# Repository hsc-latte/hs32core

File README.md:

# Processor

Open Source Hardware Processor

# Mission
- Reduce the barrier to entry to open source silicon for hobbyists
- Encourage the production usage of fully open source, royalty-free, community designed ASICs within the maker community (displace proprietary chip designs)
- Shorten the iteration time from ideation to fabrication
- Explore creative ideas not found in current hardware offerings
- Interoperate with modern, high performance components that are typically the realm of proprietary designs (DDR4, PCIE root complex, USB3, etc come to mind)
- Make easy to use, relatively inexpensive hardware that people can acutally buy

# Project Goals

## Processor V1 (November 2020)
The software and the hardware parts can mostly be done simultaneously.
1. Create a new CPU instruction set and design.
    - it should be a sort of minimum viable 32 bit CPU. Something similar in capability to an Arduino, and with similar ports.
2. Test the CPU design in simulators and on FPGA
3. Fabricate the processor using Google and efabless free shuttle service for open source using 130nm process, and open source PDK
    - Submit a design for the November free shuttle run.
    - Try not to go too crazy with transistor count. We want to not be dependent on free fabrication in the future.
4. Build an assembler for the ISA
5. Make an Arduino-like board for the processor, with similar capabilities and supporting software
6. Write or port C toolchain. Some higher level languages would also be nice, such as JS/python.
    - [TCC](https://bellard.org/tcc/) may be a good compiler to retarget for C.
        - [Here](https://bellard.org/tcc/tcc-doc.html#CPU-dependent-code-generation) is what would be needed to be done to retarget it.
    - Port as much of libc as possible. [Uclib-ng](https://www.uclibc-ng.org/) or [newlib](https://sourceware.org/newlib/) would be good options.

### Task List for V1 by Early November 2020 (exact deadline date to be determined):
- Design FPGA carrier board PCB. Get it manufactured, into peoples hands.
  - This board has this FPGA board on it, https://www.robotshop.com/en/devantech-icewerx-ice40-hx8k-fpga.html?utm_source=google&utm_medium=surfaces&utm_campaign=surfaces_across_google_usen&gclid=EAIaIQobChMI5cem_Lyv6wIV0yCtBh2KFQhIEAYYASABEgJyuvD_BwE
  - The board has SRAM and Flash chips built in.
  - The board has latch chips to function as IO expanders because the fabricated CPU will be pin-limited.
  - The board should have its own clock IC.
- Design ISA
- Write assembler for the ISA
- Get Verilog simulator up and running and documented.
- Design CPU and peripherals in Verilog or Migen. 
- Simulate CPU and periherals in software. Programs should be able to run and take input/output. 
- Test CPU and peripherals on the FGPA carrier board. RAM and flash should work. We should be able to load an run real programs on the board
- Create task list to prepare the verilog design for fabrication.
  - Ensure we haven't overlooked anything that could cause our design to be rejected by Google/Skywater
  - Ensure our design might actually work when fabricated

**Fun Side Project for V1** : Make an Apple II or commodore style standalone PC using the processsor.

## Processor V2 (Early 2021)
1. Replicate V1 using non-donated fabrication and make the process economically sustainable.
    - This means making chips and boards than people can actually buy.
    - See Target Silicon section below.
    - In theory, multi project wafer runs on very old tech could be < $100 per chip. Costs will go down as volume increases.
    - we could do a Kickstarter or similar to fund a larger fabrication run for V2.
2. Expand capabilities with software support
    - more RAM, faster RAM
    - graphics framebuffer
    - more ports in general.
3. Port other languages.
    - [MicroPython](https://micropython.org/) may be a good option.
    - Build a [LLVM backend](https://www.llvm.org/docs/WritingAnLLVMBackend.html).
        - This is a lot of work, so it could be done in V2 or V3.
4. A basic OS. This would be similar to old computers running BASIC. This may be porting an existing OS or writing one from sratch. 

## Processor V3 (Late 2021)
While maintaining economic sustainability:
1. Expand capabilities with software support
    - add MMU (ucLinux will run without an MMU, but typical programs will not run. They require fork() and mmap() among other MMU features.)
    - hardware floating point
    - more RAM, faster RAM
    - more ports in general. HDMI, ethernet, possibly USB and WiFi to some degree, with external chips
2. Make a raspberry-Pi style board. It would be much much slower than a Pi, but should have a similar style of capabilities and functions.
3. Port more software to the system
    - glibc should be able to be ported at this stage
4. Explore Linux support

## Processor V4 (2022)
Generally more powerful and unique. Try to achieve some interoperability with modern hardware, yet remain fully open source.
Just some ideas:
- On-chip Software Defined Radio (SDR) so that it can be a flexible radio device (WiFi, LTE, Bluetooth, GPS)
- GPU
- Multi core
- PCIE Root Controller
- DDR4 Controller
- USB3 Controller

# Educational Resources
- Reading list for newcomers to computer engineering, started here: [link](Resources.md)

# CPU for V1

- 32 bit
- flat address space, no MMU
- As simple as possible
- Should support running unmodified C programs.
- Required math ops: the usual AND OR NOT XOR shifts, rotates.
- Integer multiply and divide would be cool if we can fit it.
- Floating point math would be cool if we can fit it, including addition,mul,div operations

# Ports for V1
The general idea is to have a superset of the peripherals that the old Arduino has.
- 14 digital 1/0
- 6 pins with PWM
- 6 analog input
  - 8 channel SPI ADC https://www.digikey.com/product-detail/en/microchip-technology/MCP3008T-I-SL/MCP3008T-I-SLCT-ND/5148847
- 4 channel SPI DAC https://www.digikey.com/product-detail/en/texas-instruments/TLV5620IDR/296-41707-2-ND/1669684
- SPI/I2C/I2S	1/1/1
- SRAM: http://www.issi.com/WW/pdf/62WV12816ALL.pdf
- Flash: S29AL008J https://www.cypress.com/file/216396/download
- External Clock of at least 16mhz
- USB port for programming (FTDI chip?)
- PS2 mouse, keyboard
  - https://opencores.org/projects/ps2
- 4 Serial Ports (UART)
  - https://opencores.org/projects/uart16550
  - https://opencores.org/projects/uart
- Ethernet
  - Ethernet likely takes too many gates, but we can have an external chip:
  - Using this chip which offloads most of the harder networking work and you just need to talk to it over SPI.
   - https://wizwiki.net/wiki/lib/exe/fetch.php?media=products:w5100s:w5100s_ds_v100e.pdf
   - https://www.digikey.com/products/en?keywords=W5100S
   - in fact it does TCP and UDP for you!
- Display: NTSC Composite Video Out
  - ntsc https://webcache.googleusercontent.com/search?q=cache:4BF235L2FPcJ:https://opencores.org/projects/fbas_encoder+&cd=1&hl=en&ct=clnk&gl=us
- SD Card or Compactflash or something similar
- If we want we can add a USB host using an external chip https://www.hobbytronics.co.uk/usb-host-dip

# Target Silicon:
### Google-skywater november 2020 free shuttle run
- Info collected from skywater-pdk slack:
- Tim Edwards: The whole chip will be (provisionally) 3.2 x 5.3, but the user area will be about 9 to 10 mm^2.  That is not including the pad frame;  that's the full core area you get to use.  I'm aiming to keep the "management region" off to one side to keep the user area roughly square.  The pads are 200um high, so the height is limited to 2.8mm, so the area you get to work with will be around 3.2 to 3.5mm wide and 2.8mm high.
- Packaging: WLCSP: Main reason for wlcsp packaging is reduced parasitics for high speed signals like SERDES etc. Wlcsp is done before cutting the wafer so it doesn't require a separate packaging line.
- Pins: Expected usable pins is more ~ 40

### Non-Google, more sustainable options:
- Silicon price list exploration: https://docs.google.com/spreadsheets/d/1oqIo1lJNRx8SugjHd8WOBk07iPeCCzOLdnaOR9BBdXU/edit#gid=0
- 700nm process from ON Semi 
- 5 mm^2 of this tech: ON Semi 0.7µ C07M-D 2M/1P
- Silicon Fab price list: https://europractice-ic.com/wp-content/uploads/2020/07/General-MPW-EUROPRACTICE-200714-v11.pdf
- Another price list from europractice... https://europractice-ic.com/wp-content/uploads/2020/05/Miniasic-MPW-EUROPRACTICE-200505-v5.pdf
- Packaging: https://europractice-ic.com/packaging-integration/standard-packaging/
- Bond pad design for wirebonding https://europractice-ic.com/wp-content/uploads/2020/06/ASIC-Package-Design-Rules-10062020.pdf
- How many pins can the processor have? chip side length/distance between pads: sqrt(5mm^2) / 65um = 34. To be conservative, round to 30 pads per side. Therefore, estimate maximum 120 total pins for the entire chip. Ceramic quad flat pack (QFP) is available with that many pins from europractice.
- How much of the die area is dedicated to wire bonding pads? Assume bond pad is 60um. 4 * 60um * sqrt(5mm^2) = .536 mm^2
  - Therefore approximately 10% of the die ares is wire bonding pads. Not too bad.
- I would guess theres about 30000 to 8000 transistors per mm^2
- Therefore at 5mm^2, we have 150k to 40k transistors per chip. (it will be less due to the edge ring area being used for other stuff)
- It should be 4 transistors per gate
- so 37k to 10k gates per chip
- on-chip memory:
  - It looks like a CMOS SRAM cell has 6 transistors ... for 1 bit of storage.
  - If the entire die was made into SRAM we would therefore get 25kbit to 6.6kbit, or 3.2KB to .8KB
- The most basic ZPU (which is a tiny processor) calls for "about 1700 gates"

# Interesting Tools

- Long list of companies offering Multi Project Wafer services https://www.mirrorsemi.com/Foundry.html
- A Python toolbox for building complex digital hardware https://github.com/m-labs/migen
- Generates a custom CPU based on C code tailored to your code https://github.com/dawsonjon/Chips-2.0
- Open Source VLSI toolbox http://opencircuitdesign.com/magic/
- EDAlyze - python scripting of EDA tools https://github.com/olofk/edalize
- Package manager for IP cores https://github.com/olofk/fusesoc
- *** OpenLane - fully automated RTL to ASIC flow. https://github.com/efabless/openlane
- APIO - open ecosystem for FPGA boards https://github.com/FPGAwars/apio
- 130nm process design kit (PDK) from skywater https://github.com/google/skywater-pdk

# License 

- GPL v3

# VGA Notes
  - https://webcache.googleusercontent.com/search?q=cache:uBfl2FENLigJ:https://opencores.org/projects/yavga+&cd=2&hl=en&ct=clnk&gl=us
  - really not sure if we can do video out without a framebuffer, and then if we can get fast enough external RAM to use as a framebuffer.
  - possible expensive memory chip: https://www.digikey.com/product-detail/en/renesas-electronics-america-inc/70V28L20PFGI/800-2108-ND/2010195
   - it is dual port so it can simultaneous read and write (great for framebuffers)
   - asynchronous SRAM
   - parallel addr/data bus, 16 bit
   - full speed should be 50Mhz @ 16 bit accesses
   - The VGA core has a 50Mhz pixel clock so it should be possible to do color at 800x600!

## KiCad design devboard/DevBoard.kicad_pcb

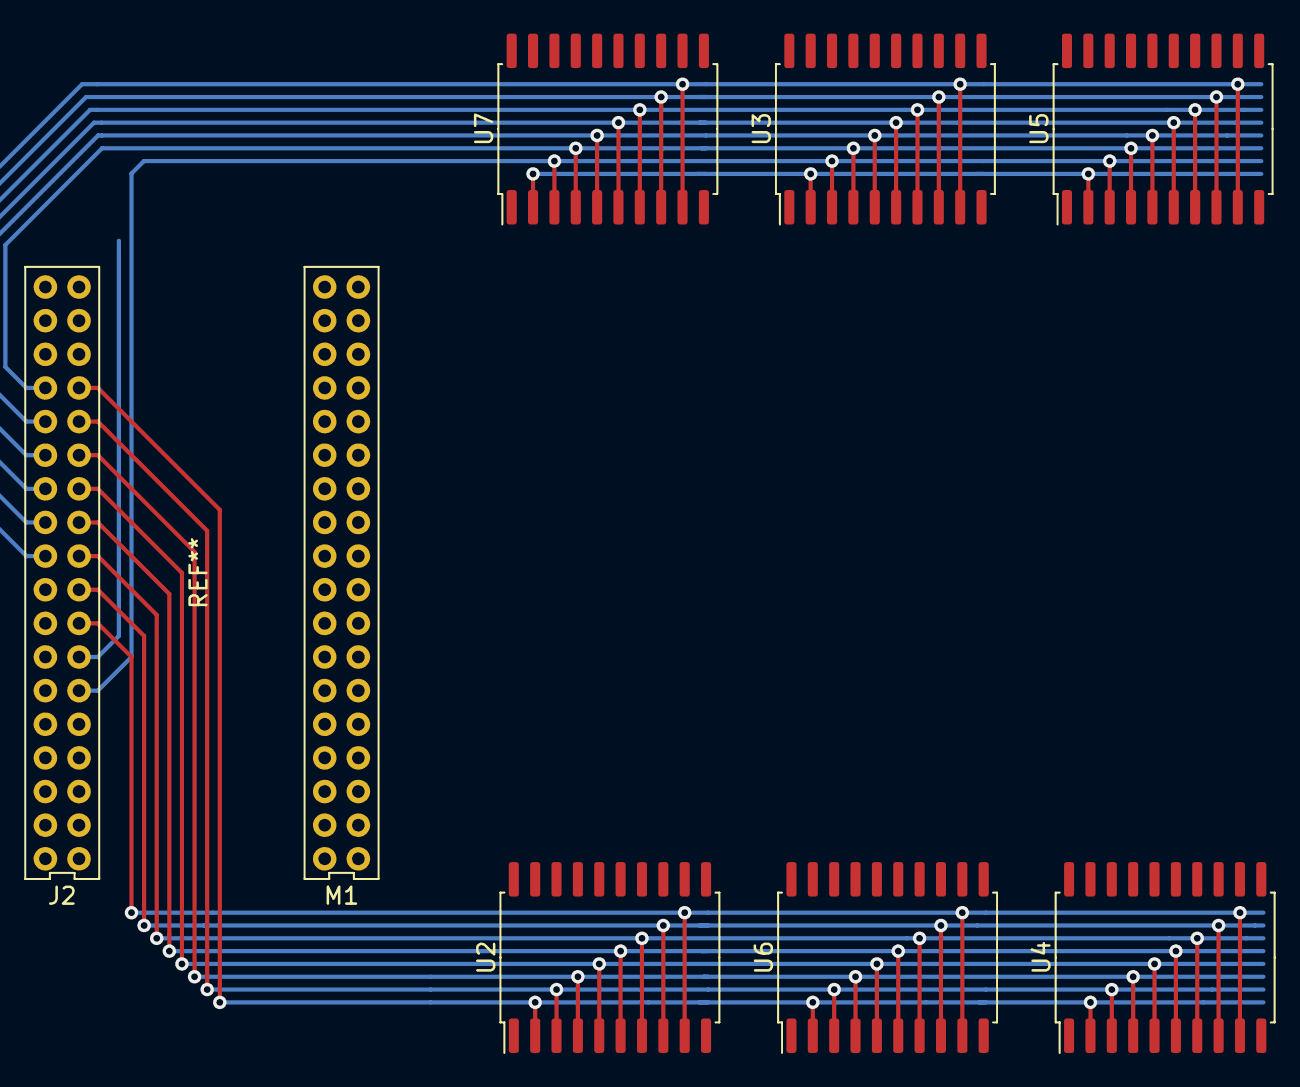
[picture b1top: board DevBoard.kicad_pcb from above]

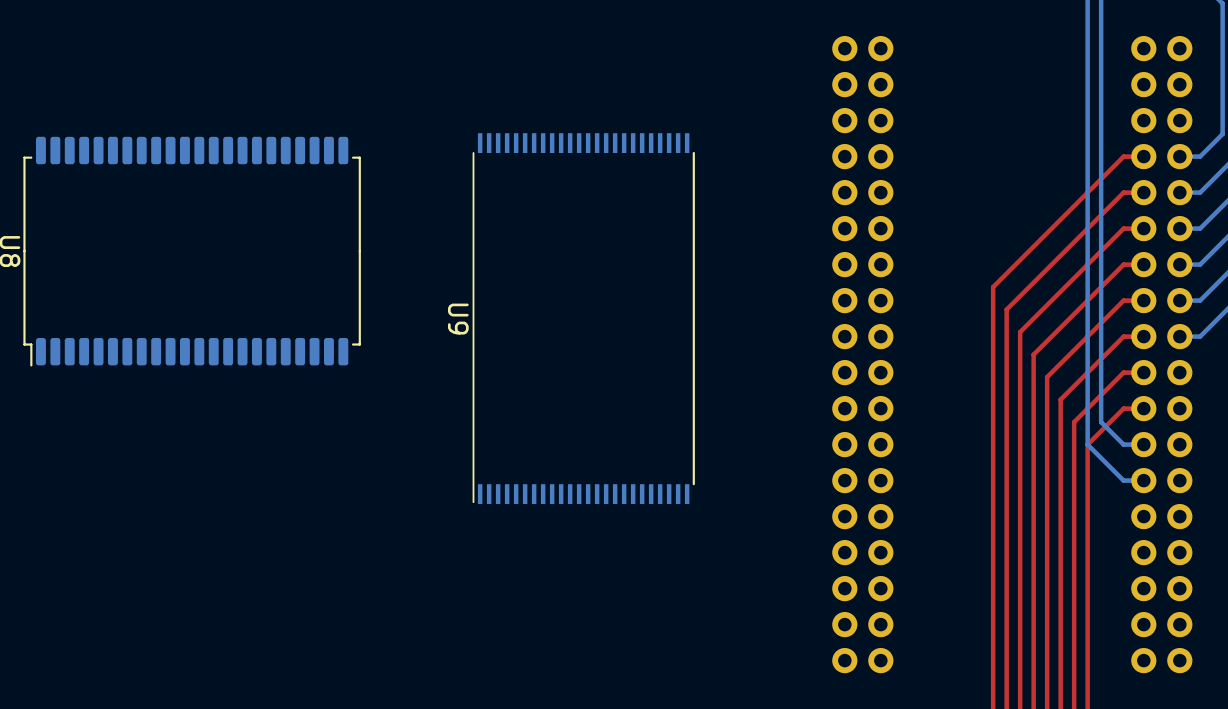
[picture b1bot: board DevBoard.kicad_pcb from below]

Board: 2 copper layers, 9 parts (2 on the bottom side), 43 nets.

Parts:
M1: icewerx; iceWerx
U2, U3, U4, U5: 74HC573; SOIC-20W_7.5x12.8mm_P1.27mm
U6, U7: 74HC245; SOIC-20W_7.5x12.8mm_P1.27mm
U8: IS62WV12816ALL; TSOP-II-44_10.16x18.41mm_P0.8mm
U9: S29AL008J70TFI013; TSOP-I-48_18.4x12mm_P0.5mm

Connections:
+3V3: U2.20, U3.20, U4.20, U5.20, U6.20, U7.20
/3.3V: U8.11, U8.33, U9.12, U9.14, U9.37, U9.47
/A0: U2.19, U8.5, U8.39, U9.25
/A1: U2.18, U8.4, U9.24
/A2: U2.17, U8.3, U9.23
/A3: U2.16, U8.2, U9.22
/A4: U2.15, U8.1, U9.21
/A5: U2.14, U8.44, U9.20
/A6: U2.13, U8.43, U9.19
/A7: U2.12, U8.42, U9.18
/A8: U3.19, U8.27, U9.8
/A9: U3.18, U8.26, U9.7
/A10: U3.17, U8.25, U9.6
/A11: U3.16, U8.24, U9.5
/A12: U3.15, U8.22, U9.4
/A13: U3.14, U8.21, U9.3
/A14: U3.13, U8.20, U9.2
/A15: U3.12, U8.19, U9.1
/A16: U4.19, U8.18, U9.48
/A17: U4.18, U9.17
/A18: U4.17, U9.16
/A30: U5.13, U9.26
/A31: U5.12, U8.6
/ALE1: U4.11, U5.11
/IO0: M1.J2.30, U2.2, U4.2, U6.2, U8.7, U9.29
/IO1: M1.J2.28, U2.3, U4.3, U6.3, U8.8, U9.31
/IO2: M1.J2.26, U2.4, U4.4, U6.4, U8.9, U9.33
/IO3: M1.J2.24, U2.5, U4.5, U6.5, U8.10, U9.35
/IO4: M1.J2.22, U2.6, U4.6, U6.6, U8.13, U9.38
/IO5: M1.J2.20, U2.7, U4.7, U6.7, U8.14, U9.40
/IO6: M1.J2.18, U2.8, U4.8, U6.8, U8.15, U9.42
/IO7: M1.J2.16, U2.9, U4.9, U6.9, U8.16, U9.44
/IO8: M1.J2.14, U3.2, U5.2, U7.2, U8.29, U9.30
/IO9: M1.J2.12, U3.3, U5.3, U7.3, U8.30, U9.32
/IO10: M1.J2.29, U3.4, U5.4, U7.4, U8.31, U9.34
/IO11: M1.J2.27, U3.5, U5.5, U7.5, U8.32, U9.36
/IO12: M1.J2.25, U3.6, U5.6, U7.6, U8.35, U9.39
/IO13: M1.J2.23, U3.7, U5.7, U7.7, U8.36, U9.41
/IO14: M1.J2.21, U3.8, U5.8, U7.8, U8.37, U9.43
/IO15: M1.J2.19, U3.9, U5.9, U7.9, U8.38, U9.45
/OE: U6.19, U7.19
/WE: U6.1, U7.1, U8.17, U9.11
GND: U2.10, U3.1, U3.10, U4.1, U4.10, U5.1, U5.10, U6.10, U7.10, U8.12, U8.34, U8.41, U9.27, U9.28, U9.46

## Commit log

2020-07-30 add some links to open cores and some hardware
2020-07-31 add a simple python emulator
2020-08-02 Update LICENSE
2020-08-04 rename
2020-08-07 Create Resources.md
    wiki type file for general knowledge resources
2020-08-10 Add mission
2020-08-11 Added magic tool
2020-08-11 Added yosys and misc changes
    Added yosys, added source github repo to README.md, and echoed the link
    of the VNC client for the magic tool when run.
2020-08-11 Reformatted tools/README.md and added docker sources
2020-08-17 Add some google-skywater info
2020-08-18 Added software goals to project goals
2020-08-22 Addded documentation and timing
2020-08-22 Edits
2020-08-26 wiznet chip link
2020-08-29 Rough draft of ISA
    Rough draft of a 32-bit hex ISA
2020-08-29 Updated some things
2020-08-29 Updated documentation.
2020-08-29 Yes oops forgot about this one.
2020-08-31 add docker notes for RTL stuff
2020-08-31 Updated rtl/README
2020-08-31 get APIO packages installed properly
2020-08-31 Updated CPU.md
2020-08-31 Added Development PCB Schematic
2020-09-01 Added Flash
2020-09-05 Updates v2
2020-09-07 Partially completed instruction set
2020-09-08 Update ISA
2020-09-09 Minor adjustment to ISA
2020-09-11 Add ADDI instruction
2020-09-12 update verilator in docker - get a test verilator running
2020-09-12 add some hacked together wbuart
2020-09-12 add docker stuff for wbuart
2020-09-13 Board modifications
2020-09-14 Updated ISA
2020-09-14 Table
2020-09-14 Try again haha
2020-09-14 Pretty?
2020-09-14 Revert!
2020-09-19 Oh well
2020-09-19 add opcodes for new emulator
2020-09-21 Idk...
2020-09-23 No more Rm Rn operands!
2020-09-23 Update ISA encoding and table
2020-09-24 Update ISA J-Type encoding
2020-09-24 Scanner, CLI, and Dockerfile for the assembler
2020-09-24 Added small README.md
2020-09-24 Remove lock file
2020-09-26 K there
2020-09-26 Updated block
2020-09-26 remove uart example
2020-09-26 new devboard project so i can do this in altium faster
2020-09-27 footprint and symbols
2020-09-27 working on FPs and symbs
2020-09-27 working on schematic
2020-09-27 made some schematic changes. added gitignore. added somemore files.added pdf for viewing
2020-09-27 schematic work. new pdf.
2020-09-27 schematic work. updated pdf. shifted A0 out for BLE
2020-09-28 schematic work. updated pdf.
2020-09-28 annotated. imported to pdf. assigned some FPs
2020-09-29 Adds parser for the assembler
    This parses the op codes. checks the instructions have the right arity,
    and checks that the values have valid types (e.g register or imm)
    This also builds a symbol table for the labels.
    This also does some refactoring here and there.
2020-09-29 schematic work. finalizing address pins, etc. adding more peripherals. latest pdf generated.
2020-09-29 updated git ignore
2020-09-29 schematic work, placed LDO
2020-09-30 finished up schematic for now
2020-09-30 updated power input to allow for 5v external power. added debounce cap to reset button. printed new pdf
2020-09-30 working on pcb
2020-09-30 layout work
2020-10-02 layout work. completed intial data bus routing
2020-10-02 layout work. control signals
2020-10-02 layout work. GPIO. reset
2020-10-03 layout work. mainly routed
2020-10-03 layout work. clearing drc. printed prints
2020-10-03 designators. cleanup.new prints
2020-10-03 Add implementation of encoding and decoding instructions
    This adds an implementation of encoding Instruction objects into bytes
    and vice versa. This does not fully add the details of the ISA and its
    encoding.
2020-10-04 finishing up. set mfr part numbers for bom. drawings. etc.
2020-10-04 fixed an issue with board outline. regenerated files
2020-10-04 outjob tweak
2020-10-06 FPGA quick guide - needs update
2020-10-06 FPGA guide added info
2020-10-10 adding output files and outjob
2020-10-11 changed switch, latch, and LED FP and pns for use with JLC PCB. created new FPs.
2020-10-11 updated layout for parts changes. passes DRC. generated outputs.
2020-10-12 updated files
2020-10-13 added more pnp files
2020-10-13 changed flash chip. hooked up 3 additional adddress lines. routing work. tented all vias. added Rev 1.3 to silk. clean up. printed new outputs
2020-10-21 Finish the assembler
2020-10-21 Fixes the pypi and docker builds
    This allows this to be run from pypi and changes the docker build to use
    that. This also has some code formatting.
2020-10-23 Added vscode build configuration
2020-10-23 Slowly get the ball rolling
2020-10-23 In-house IceWerx programmer (console)
2020-10-23 Minor edits, added license
2020-10-23 Added binaries for now (too lazy)
2020-10-23 Fix bug
2020-10-23 Updated tooling information
2020-10-24 regenerated files, added a bunch of files
2020-10-25 Added basic module declarations
2020-10-27 Update FPGA documentations
2020-10-27 Fixed FPGA docs error
2020-10-31 Defined Register File I/O
2020-10-31 Finished Decode Module
    - Added active low reset
    - Added imm5 and imm24 outputs
    - Added regopd output as Rn
    - Added instruction prefix addressing mode matching
2020-10-31 Update Fetch Module
    - Added active low reset and active high flush
    - Added program counter rewrite
    - Added memory request function
    - Added pseudo Fetch function
    - Added pseudo Output function
2020-10-31 Added Pipeline Module
2020-10-31 Added ALU Module
2020-10-31 Updated Register File Module
    - Added pseudo function to identify registers
2020-10-31 Updated Execution Module
    - Matched I/O with Decode Module
2020-10-31 Added SoC and testing modules
2020-10-31 Fixed some invalid code
2020-10-31 Fixed Decode Module Bugs
    - Fixed decode not validating instruction input
    - Fixed multiple sensitivity errors
2020-10-31 Update pcf comments
2020-10-31 Update tasks again
2020-10-31 Update FPGA Pin Assignment
2020-10-31 Fixed Fetch Module Bugs
    - Fixed multi sensitivity errors
2020-11-01 Updated pin assignment
    - Added additional Dev Board pins
    - Renamed iCE40-HX8K.pcf to hsc.pcf
2020-11-01 Update Example Makefile
    - Changed Physical Constraints File PCF name to match updated file
2020-11-01 Fixed Physical Constraints File Error
    - Fixed reset pin not found error
    - Added 2 missing pins
2020-11-01 Update Makefile
    - Changed hard coded library to variable
2020-11-01 Update Example Verilog
    - Added all I/O pins
    - Added dev board GPIO LED test
2020-11-01 Fixed Example Verilog GPIO Test
    - Fixed GPIO test not repeating error
2020-11-01 Added SRAM controller
2020-11-01 Whoops
2020-11-01 Testbench
2020-11-01 Finished up wiring all the important files
2020-11-01 Update SRAM Testbench
    - Added testbench variables
    - Added SRAM Module
    - Added simulation initialization
    - Added simulation clock
    - Added Read Mode simulation
    - Added Write Mode simulation
2020-11-01 Fixed minor bug and improved logic count
2020-11-01 Update SRAM Testbench
    - Fixed compiling errors
    - Optimized tests
2020-11-01 Fixed SRAM Bugs
    - Fixed fsm undefined
    - Fixed fsm reset
2020-11-01 Added a basic SoC + memory controller for testing
2020-11-01 Fixed SRAM Module Bugs
    - Fixed fsm undefined issue
2020-11-01 Fixed bug
2020-11-01 Fixed ALE undefined error
2020-11-01 Reorder the testbenches
2020-11-04 Fixed sram driver and added test programmer
2020-11-14 100% Anthony's Idea yes
2020-11-14 Added specs for control signals
2020-11-14 Minor update
2020-11-14 Finished documentation
2020-11-14 Updated documentation
2020-11-15 Reworked ISA, started execute and decode
    - Removed MOVT
    - Drafted interrupts
    - Fixed register banks
    - Completed shift and format descriptions
    - Revised ctlsigs
2020-11-15 I forgot about branch-and-link haha
2020-11-16 Added Decode Unit Instruction Formatting
2020-11-16 Update ALU Operation Codes
2020-11-16 Update ISA operations
2020-11-16 Include Instruction Formatting
2020-11-16 Update ISA (yes I've kidnapped Kevin's github >:]
2020-11-16 Well hello :P yes blame Kevin for everything >:]
2020-11-16 Hey >:[
2020-11-16 Removed MOVT from OP Codes
    - Removed MOVT from OP Codes
    - Also testing my Git XD
2020-11-17 Started work on fetch.v
2020-11-17 First verification! Formally verified bram_ctl
2020-11-17 Updated proof
2020-11-18 Big endian because Anthony :3
2020-11-18 Fixed ISA Instruction Size Error
    - Instruction size wrongly set to 36 bits, changed to 32 bits
    - ISA correct instrcution size is 32 bits
2020-11-18 Fixed ISA I-Type Instruction Formatting
    - Fixed Rn appear in I-Type instruction
    - I-Type instruction have no Rn values
2020-11-18 Fixed ISA Error Again (Sorry :C)
2020-11-19 Finished and verified prefetch module
    - Updated proof for soc bram
    - Added proof for prefetch
    - Added proof for mem
    - Started to rename ack to rdy (we should use valid & ready handshake)
2020-11-19 Revised proof
2020-11-20 Update ISA Register Bank and MOV Instruction
    - Changed clarification on register bank field
    - Changed MOV Rd <- Rm instruction to MOV Rd <- Rm_b to include bank
    - Added MOV Rd_b <- Rm instruction variant 010
2020-11-20 Added Carry Operations
    - Changed ALUOPS to 4 bits
    - Added Carry operations
2020-11-20 Added MOVR Instruction
    - Changed MOV instruction to include bank information
    - Added MOVR instruction
2020-11-20 Changed ISA Decoding - No Changes to OP Codes
    - Added Reverse Bus Indicator
    - Removed Interrupt Request
    - Added Bank Register Indicator
    - Removed Shift Direction in LDR STR MOV Rm variants
    - Fixed CMP TST Rn without sh()
    - Fixed terminology inconsistencies
2020-11-20 Fixed ALUOP and OPCODES Naming Conflicts
    - Added prefix A for ALUOPS
2020-11-20 Added NOP for ALUOPS
2020-11-20 Update ISA for ALUOPS
2020-11-20 Update Decode Unit
    - Added all instructions OP Codes
2020-11-21 Updated license (all contributors consent)
2020-11-21 Update fetch
2020-11-21 Finished execution unit changes
2020-11-22 1 cycle latency babyyyyyyyy
    - Committed tests
2020-11-22 Moved cores to third_party and added LICENSE
2020-11-22 Added branching to execute
2020-11-22 Updated file headers
2020-11-23 files to make the prechecker happy
2020-11-24 Updated execute, fixed decode, fixed branching
2020-11-24 Finished wiring all core modules
2020-11-28 Openlane config
2020-11-29 Updated config
2020-11-29 Update gitignore
2020-11-29 Added Interrupt Table
2020-11-29 Update ISA Notes
2020-11-29 Added Interrupt Module
2020-11-29 Added Interrupt Support
2020-11-30 Update Decode
    - Changed Shift to 0 for all ignores
    - Update interrupt instruction
2020-11-30 Fixed.
2020-11-30 Ree.
2020-11-30 Wishbone interface slowly being made
2020-11-30 Updated Interrupt Table
2020-11-30 Fixed Decode Errors
2020-11-30 Update MMIO Interrupts
2020-11-30 Added MMIO Docs
2020-11-30 NMI for Interrupts
2020-11-30 Moved RTL to new repo
2020-11-30 Added RTL back as submodule
2020-12-01 Update sub
